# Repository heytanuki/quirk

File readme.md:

# Quirk
An asymmetric 50% ortholinear that supports 60s key sets. Wide side keys to easily find them. Rough edges.

### issues
- currently this repo might be in a bad state because it was the first i created. working on remaking this better.

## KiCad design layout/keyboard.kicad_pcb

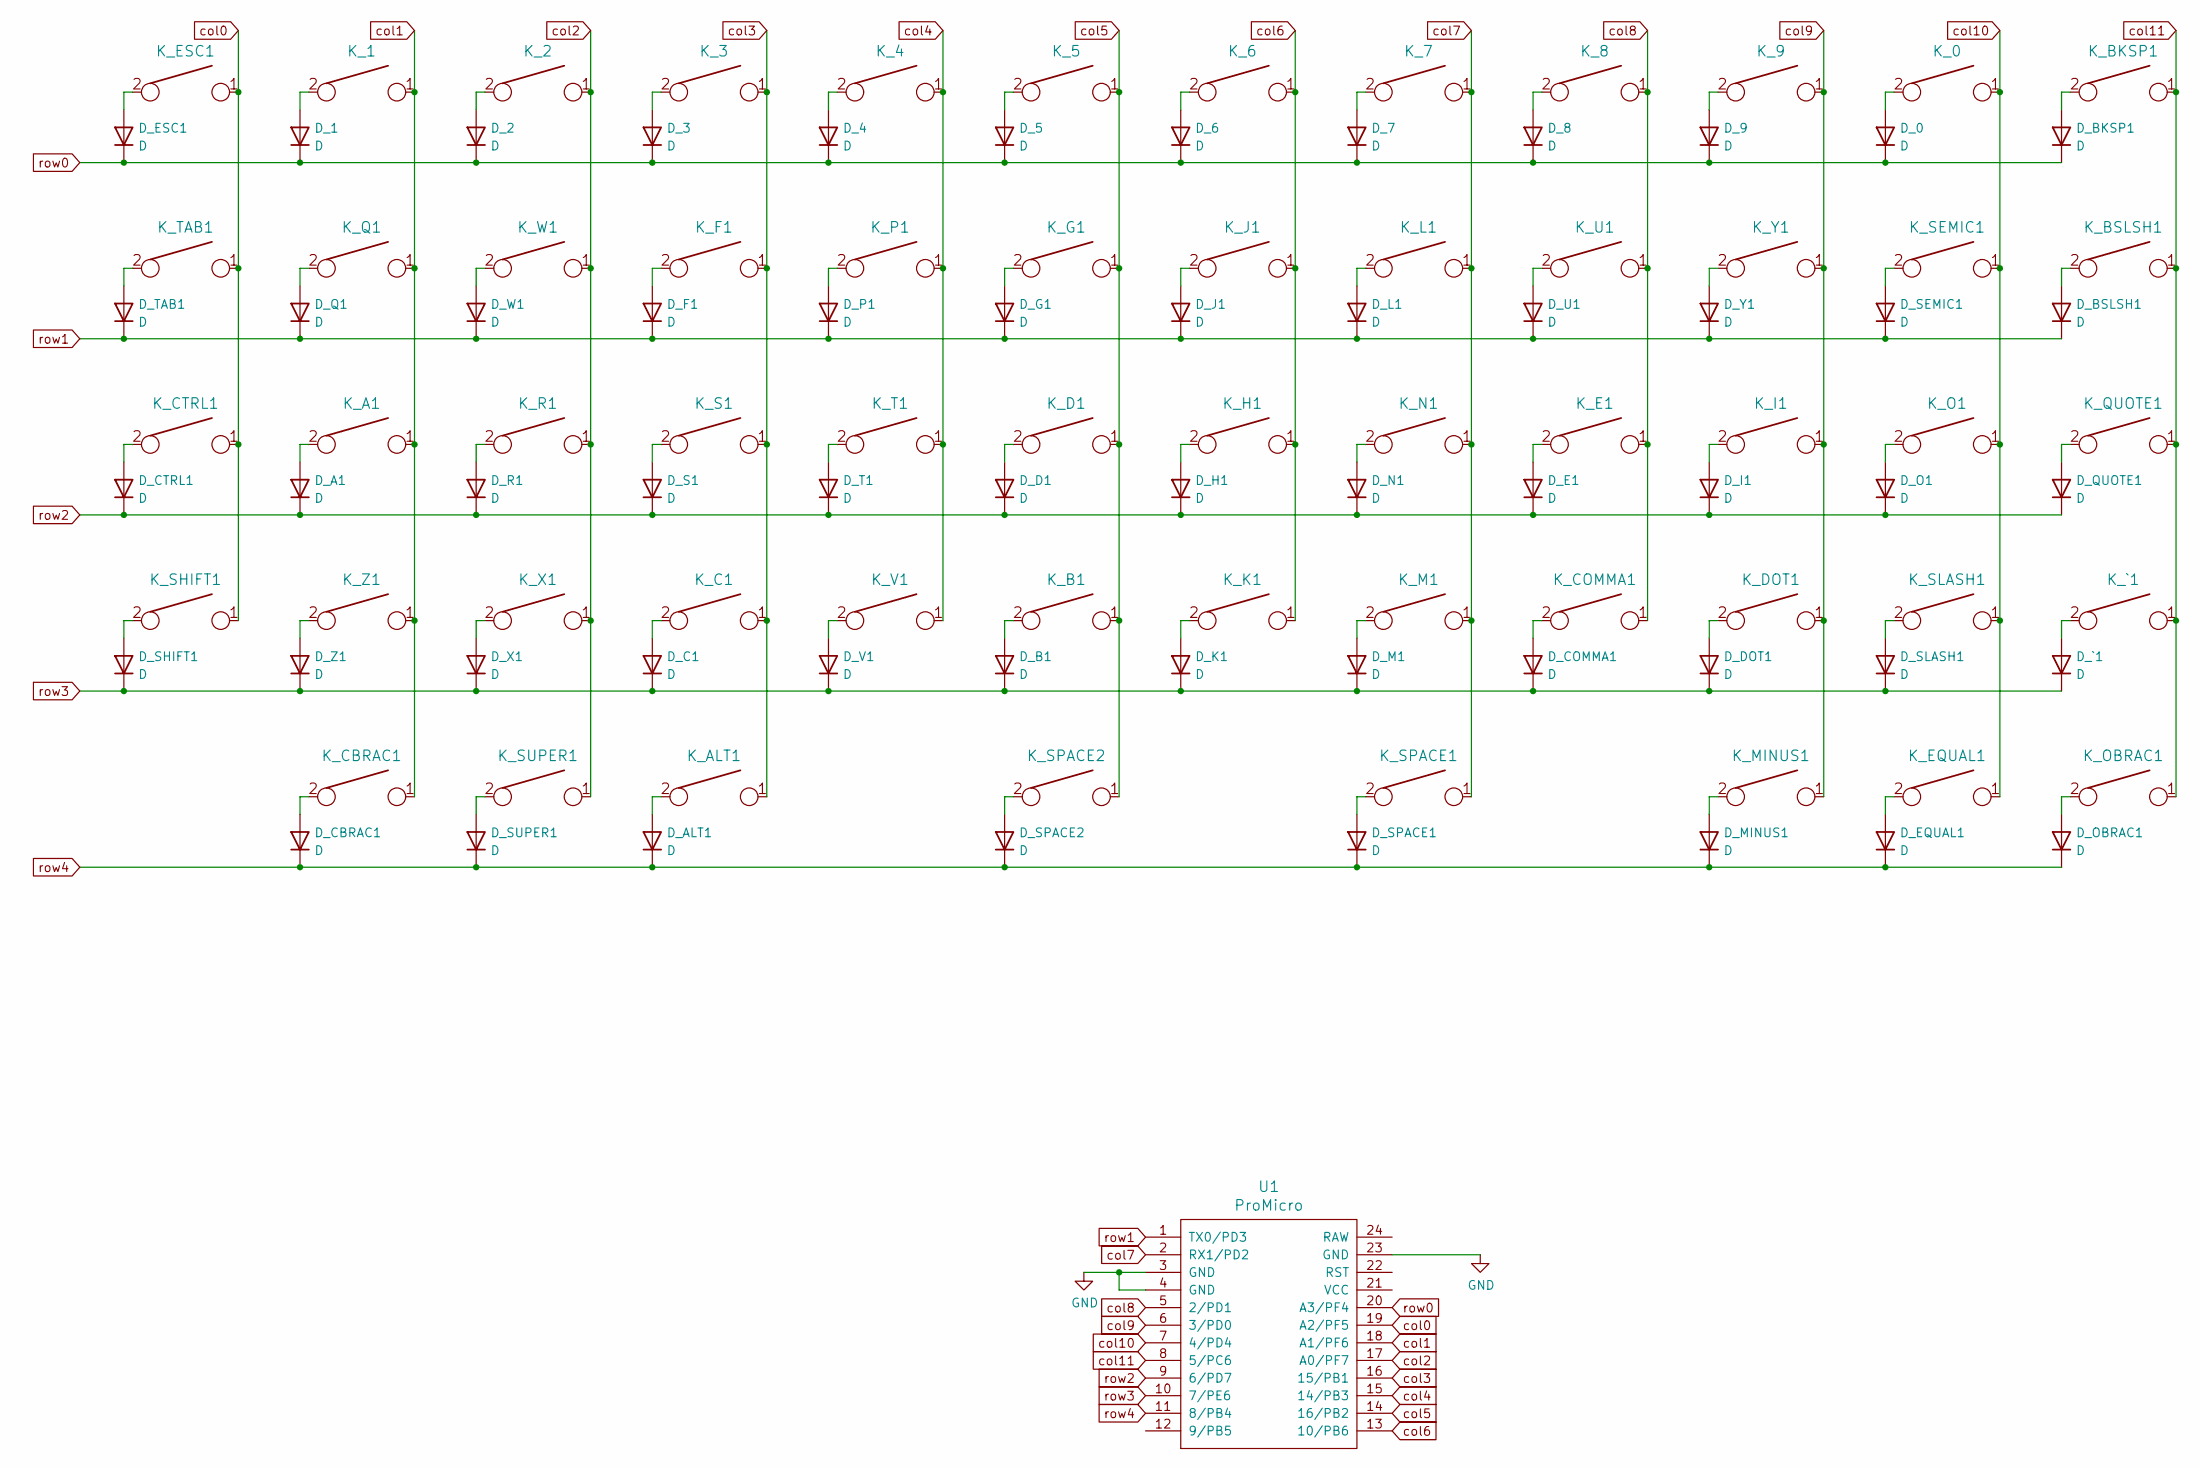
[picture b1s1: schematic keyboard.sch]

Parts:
D_0, D_1, D_2, D_3, D_4, D_5, D_6, D_7, D_8, D_9: D; D_SOD-123
D_A1: D; D_SOD-123
D_ALT1: D; D_SOD-123
D_B1: D; D_SOD-123
D_BKSP1: D; D_SOD-123
D_BSLSH1: D; D_SOD-123
D_C1: D; D_SOD-123
D_CBRAC1: D; D_SOD-123
D_COMMA1: D; D_SOD-123
D_CTRL1: D; D_SOD-123
D_D1: D; D_SOD-123
D_DOT1: D; D_SOD-123
D_E1: D; D_SOD-123
D_EQUAL1: D; D_SOD-123
D_ESC1: D; D_SOD-123
D_F1: D; D_SOD-123
D_G1: D; D_SOD-123
D_H1: D; D_SOD-123
D_I1: D; D_SOD-123
D_J1: D; D_SOD-123
D_K1: D; D_SOD-123
D_L1: D; D_SOD-123
D_M1: D; D_SOD-123
D_MINUS1: D; D_SOD-123
D_N1: D; D_SOD-123
D_O1: D; D_SOD-123
D_OBRAC1: D; D_SOD-123
D_P1: D; D_SOD-123
D_Q1: D; D_SOD-123
D_QUOTE1: D; D_SOD-123
D_R1: D; D_SOD-123
D_S1: D; D_SOD-123
D_SEMIC1: D; D_SOD-123
D_SHIFT1: D; D_SOD-123
D_SLASH1: D; D_SOD-123
D_SPACE1, D_SPACE2: D; D_SOD-123
D_SUPER1: D; D_SOD-123
D_T1: D; D_SOD-123
D_TAB1: D; D_SOD-123
D_U1: D; D_SOD-123
D_V1: D; D_SOD-123
D_W1: D; D_SOD-123
D_X1: D; D_SOD-123
D_Y1: D; D_SOD-123
D_Z1: D; D_SOD-123
D_`1: D; D_SOD-123
K_0, K_1, K_2, K_3, K_4, K_5, K_6, K_7, K_8, K_9: KEYSW; MXOnly-1U-Hotswap
K_A1: KEYSW; MXOnly-1U-Hotswap
K_ALT1: KEYSW; MXOnly-1.25U-Hotswap
K_B1: KEYSW; MXOnly-1U-Hotswap
K_BKSP1: KEYSW; MXOnly-2U-Hotswap
K_BSLSH1: KEYSW; MXOnly-1.5U-Hotswap
K_C1: KEYSW; MXOnly-1U-Hotswap
K_CBRAC1: KEYSW; MXOnly-1U-Hotswap
K_COMMA1: KEYSW; MXOnly-1U-Hotswap
K_CTRL1: KEYSW; MXOnly-1U-Hotswap
K_D1: KEYSW; MXOnly-1U-Hotswap
K_DOT1: KEYSW; MXOnly-1U-Hotswap
K_E1: KEYSW; MXOnly-1U-Hotswap
K_EQUAL1: KEYSW; MXOnly-1U-Hotswap
K_ESC1: KEYSW; MXOnly-1U-Hotswap
K_F1: KEYSW; MXOnly-1U-Hotswap
K_G1: KEYSW; MXOnly-1U-Hotswap
K_H1: KEYSW; MXOnly-1U-Hotswap
K_I1: KEYSW; MXOnly-1U-Hotswap
K_J1: KEYSW; MXOnly-1U-Hotswap
K_K1: KEYSW; MXOnly-1U-Hotswap
K_L1: KEYSW; MXOnly-1U-Hotswap
K_M1: KEYSW; MXOnly-1U-Hotswap
K_MINUS1: KEYSW; MXOnly-1U-Hotswap
K_N1: KEYSW; MXOnly-1U-Hotswap
K_O1: KEYSW; MXOnly-1U-Hotswap
K_OBRAC1: KEYSW; MXOnly-1U-Hotswap
K_P1: KEYSW; MXOnly-1U-Hotswap
K_Q1: KEYSW; MXOnly-1U-Hotswap
K_QUOTE1: KEYSW; MXOnly-1U-Hotswap
K_R1: KEYSW; MXOnly-1U-Hotswap
K_S1: KEYSW; MXOnly-1U-Hotswap
K_SEMIC1: KEYSW; MXOnly-1U-Hotswap
K_SHIFT1: KEYSW; MXOnly-2.25U-Hotswap
K_SLASH1: KEYSW; MXOnly-1U-Hotswap
K_SPACE1, K_SPACE2: KEYSW; MXOnly-2.25U-Hotswap-ReversedStabilizers
K_SUPER1: KEYSW; MXOnly-1.25U-Hotswap
K_T1: KEYSW; MXOnly-1U-Hotswap
K_TAB1: KEYSW; MXOnly-1.5U-Hotswap
K_U1: KEYSW; MXOnly-1U-Hotswap
K_V1: KEYSW; MXOnly-1U-Hotswap
K_W1: KEYSW; MXOnly-1U-Hotswap
K_X1: KEYSW; MXOnly-1U-Hotswap
K_Y1: KEYSW; MXOnly-1U-Hotswap
K_Z1: KEYSW; MXOnly-1U-Hotswap
K_`1: KEYSW; MXOnly-1U-Hotswap
U1: ProMicro; ArduinoProMicro-ZigZag

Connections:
GND: U1.3 (GND), U1.4 (GND), U1.23 (GND)
unnamed: D_0.2 (A), K_0.2
unnamed: D_1.2 (A), K_1.2
unnamed: D_2.2 (A), K_2.2
unnamed: D_3.2 (A), K_3.2
unnamed: D_4.2 (A), K_4.2
unnamed: D_5.2 (A), K_5.2
unnamed: D_6.2 (A), K_6.2
unnamed: D_7.2 (A), K_7.2
unnamed: D_8.2 (A), K_8.2
unnamed: D_9.2 (A), K_9.2
unnamed: D_A1.2 (A), K_A1.2
unnamed: D_ALT1.2 (A), K_ALT1.2
unnamed: D_B1.2 (A), K_B1.2
unnamed: D_BKSP1.2 (A), K_BKSP1.2
unnamed: D_BSLSH1.2 (A), K_BSLSH1.2
unnamed: D_C1.2 (A), K_C1.2
unnamed: D_CBRAC1.2 (A), K_CBRAC1.2
unnamed: D_COMMA1.2 (A), K_COMMA1.2
unnamed: D_CTRL1.2 (A), K_CTRL1.2
unnamed: D_D1.2 (A), K_D1.2
unnamed: D_DOT1.2 (A), K_DOT1.2
unnamed: D_E1.2 (A), K_E1.2
unnamed: D_EQUAL1.2 (A), K_EQUAL1.2
unnamed: D_ESC1.2 (A), K_ESC1.2
unnamed: D_F1.2 (A), K_F1.2
unnamed: D_G1.2 (A), K_G1.2
unnamed: D_H1.2 (A), K_H1.2
unnamed: D_I1.2 (A), K_I1.2
unnamed: D_J1.2 (A), K_J1.2
unnamed: D_K1.2 (A), K_K1.2
unnamed: D_L1.2 (A), K_L1.2
unnamed: D_M1.2 (A), K_M1.2
unnamed: D_MINUS1.2 (A), K_MINUS1.2
unnamed: D_N1.2 (A), K_N1.2
unnamed: D_O1.2 (A), K_O1.2
unnamed: D_OBRAC1.2 (A), K_OBRAC1.2
unnamed: D_P1.2 (A), K_P1.2
unnamed: D_Q1.2 (A), K_Q1.2
unnamed: D_QUOTE1.2 (A), K_QUOTE1.2
unnamed: D_R1.2 (A), K_R1.2
unnamed: D_S1.2 (A), K_S1.2
unnamed: D_SEMIC1.2 (A), K_SEMIC1.2
unnamed: D_SHIFT1.2 (A), K_SHIFT1.2
unnamed: D_SLASH1.2 (A), K_SLASH1.2
unnamed: D_SPACE1.2 (A), K_SPACE1.2
unnamed: D_SPACE2.2 (A), K_SPACE2.2
unnamed: D_SUPER1.2 (A), K_SUPER1.2
unnamed: D_T1.2 (A), K_T1.2
unnamed: D_TAB1.2 (A), K_TAB1.2
unnamed: D_U1.2 (A), K_U1.2
unnamed: D_V1.2 (A), K_V1.2
unnamed: D_W1.2 (A), K_W1.2
unnamed: D_X1.2 (A), K_X1.2
unnamed: D_Y1.2 (A), K_Y1.2
unnamed: D_Z1.2 (A), K_Z1.2
unnamed: D_`1.2 (A), K_`1.2
col0: K_CTRL1.1, K_ESC1.1, K_SHIFT1.1, K_TAB1.1, U1.19 (A2/PF5)
col1: K_1.1, K_A1.1, K_CBRAC1.1, K_Q1.1, K_Z1.1, U1.18 (A1/PF6)
col2: K_2.1, K_R1.1, K_SUPER1.1, K_W1.1, K_X1.1, U1.17 (A0/PF7)
col3: K_3.1, K_ALT1.1, K_C1.1, K_F1.1, K_S1.1, U1.16 (15/PB1)
col4: K_4.1, K_P1.1, K_T1.1, K_V1.1, U1.15 (14/PB3)
col5: K_5.1, K_B1.1, K_D1.1, K_G1.1, K_SPACE2.1, U1.14 (16/PB2)
col6: K_6.1, K_H1.1, K_J1.1, K_K1.1, U1.13 (10/PB6)
col7: K_7.1, K_L1.1, K_M1.1, K_N1.1, K_SPACE1.1, U1.2 (RX1/PD2)
col8: K_8.1, K_COMMA1.1, K_E1.1, K_U1.1, U1.5 (2/PD1)
col9: K_9.1, K_DOT1.1, K_I1.1, K_MINUS1.1, K_Y1.1, U1.6 (3/PD0)
col10: K_0.1, K_EQUAL1.1, K_O1.1, K_SEMIC1.1, K_SLASH1.1, U1.7 (4/PD4)
col11: K_BKSP1.1, K_BSLSH1.1, K_OBRAC1.1, K_QUOTE1.1, K_`1.1, U1.8 (5/PC6)
row0: D_0.1 (K), D_1.1 (K), D_2.1 (K), D_3.1 (K), D_4.1 (K), D_5.1 (K), D_6.1 (K), D_7.1 (K), D_8.1 (K), D_9.1 (K), D_BKSP1.1 (K), D_ESC1.1 (K), U1.20 (A3/PF4)
row1: D_BSLSH1.1 (K), D_F1.1 (K), D_G1.1 (K), D_J1.1 (K), D_L1.1 (K), D_P1.1 (K), D_Q1.1 (K), D_SEMIC1.1 (K), D_TAB1.1 (K), D_U1.1 (K), D_W1.1 (K), D_Y1.1 (K), U1.1 (TX0/PD3)
row2: D_A1.1 (K), D_CTRL1.1 (K), D_D1.1 (K), D_E1.1 (K), D_H1.1 (K), D_I1.1 (K), D_N1.1 (K), D_O1.1 (K), D_QUOTE1.1 (K), D_R1.1 (K), D_S1.1 (K), D_T1.1 (K), U1.9 (6/PD7)
row3: D_B1.1 (K), D_C1.1 (K), D_COMMA1.1 (K), D_DOT1.1 (K), D_K1.1 (K), D_M1.1 (K), D_SHIFT1.1 (K), D_SLASH1.1 (K), D_V1.1 (K), D_X1.1 (K), D_Z1.1 (K), D_`1.1 (K), U1.10 (7/PE6)
row4: D_ALT1.1 (K), D_CBRAC1.1 (K), D_EQUAL1.1 (K), D_MINUS1.1 (K), D_OBRAC1.1 (K), D_SPACE1.1 (K), D_SPACE2.1 (K), D_SUPER1.1 (K), U1.11 (8/PB4)

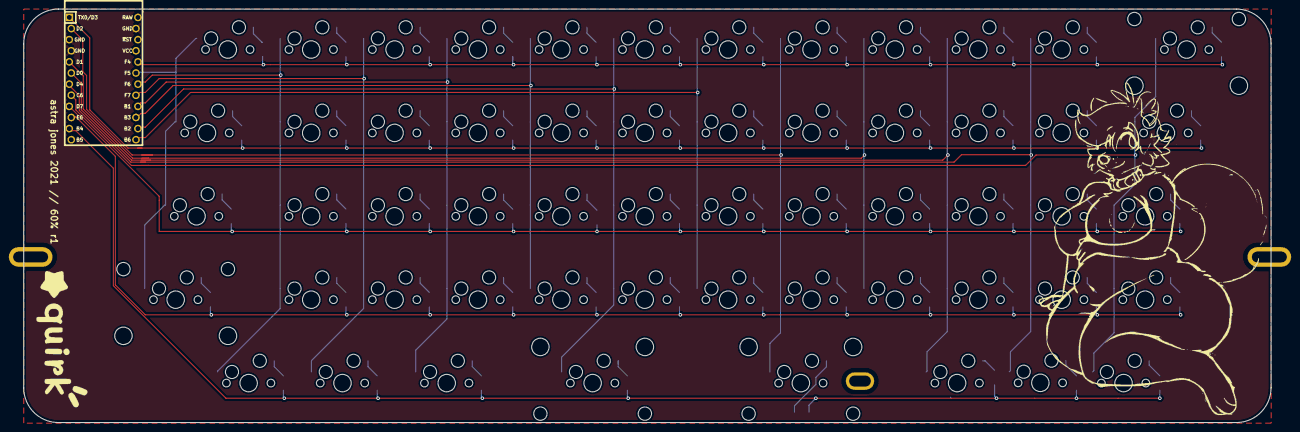
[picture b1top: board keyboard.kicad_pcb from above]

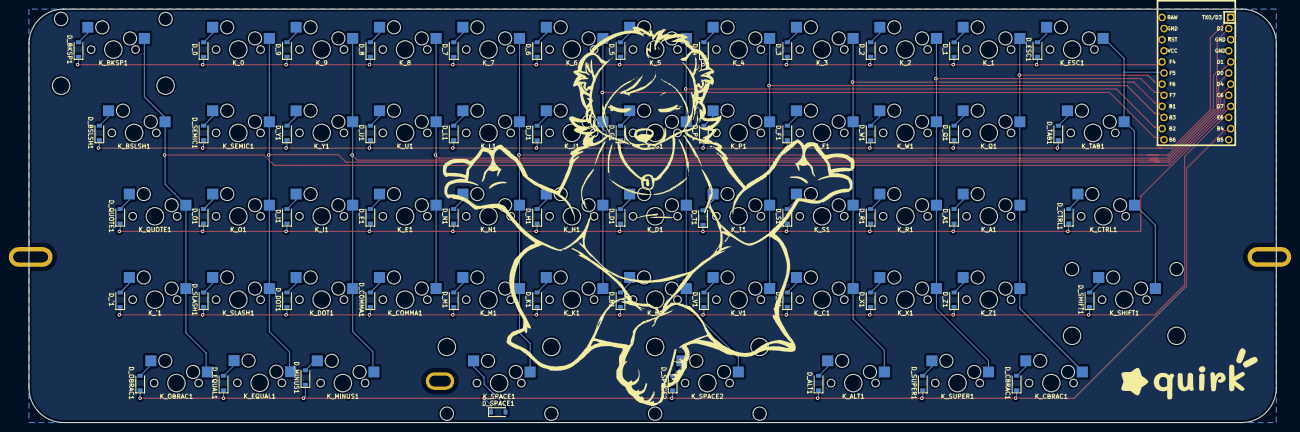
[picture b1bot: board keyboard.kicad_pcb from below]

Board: 2 copper layers, 285.0 x 94.5 mm, 116 parts (56 on the bottom side), 74 nets.

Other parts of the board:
H1, H6: Half Side Hole; halfSideHole
H4: Oval Mounting Hole; MoutingHole_Oval_7mm_5.0x2.5mm

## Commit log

2021-02-07 started pcb, add submodules
2021-02-07 switches layout
2021-02-07 unswitching cols
2021-02-08 routing to pro micro
2021-02-08 egdes, and flip diodes to back
2021-02-08 flip a label
2021-02-08 fix gnd
2021-02-08 adding KLE layout
2021-02-11 adding plate file and some silkscreens
2021-03-18 Updating with latest stuff
2021-07-23 add 60% version
2021-07-23 add readme
